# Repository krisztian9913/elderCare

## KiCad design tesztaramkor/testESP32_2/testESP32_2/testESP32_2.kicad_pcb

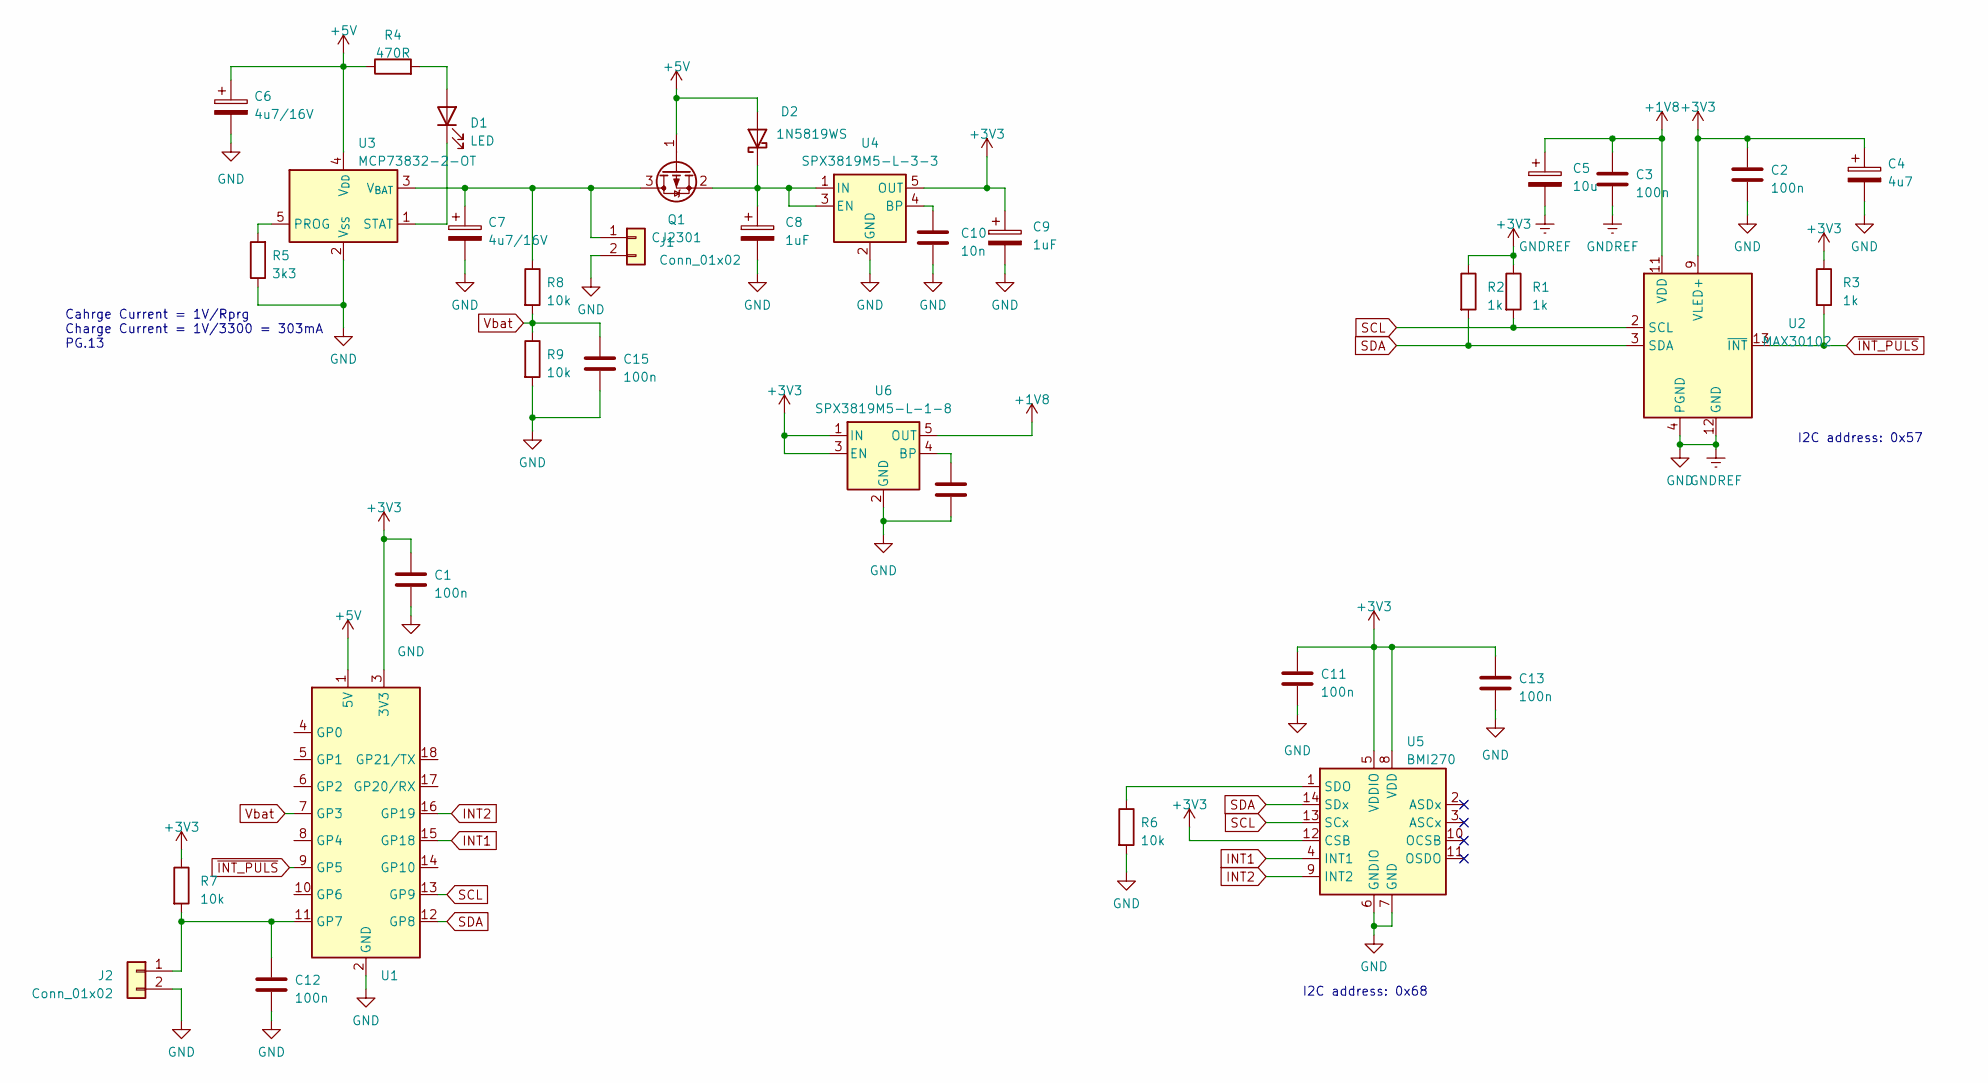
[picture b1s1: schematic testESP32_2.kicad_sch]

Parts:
C1, C2, C3, C11, C12, C13, C15: 100n; C_0603_1608Metric_Pad1.08x0.95mm_HandSolder
C4: 4u7; CP_EIA-3216-18_Kemet-A_Pad1.58x1.35mm_HandSolder
C5: 10u; CP_EIA-3216-18_Kemet-A_Pad1.58x1.35mm_HandSolder
C6, C7: 4u7/16V; CP_EIA-3216-10_Kemet-I_Pad1.58x1.35mm_HandSolder
C8, C9: 1uF; CP_EIA-3216-10_Kemet-I_Pad1.58x1.35mm_HandSolder
C10, C14: 10n; C_0603_1608Metric_Pad1.08x0.95mm_HandSolder
D1: LED; LED_0603_1608Metric_Pad1.05x0.95mm_HandSolder
D2: 1N5819WS; D_SOD-323_HandSoldering
J1, J2: Conn_01x02; PinHeader_1x02_P2.54mm_Vertical
Q1: CJ2301; SOT-23
R1, R2, R3: 1k; R_0603_1608Metric_Pad0.98x0.95mm_HandSolder
R4: 470R; R_0603_1608Metric_Pad0.98x0.95mm_HandSolder
R5: 3k3; R_0603_1608Metric_Pad0.98x0.95mm_HandSolder
R6, R7, R8, R9: 10k; R_0603_1608Metric_Pad0.98x0.95mm_HandSolder
U1: ESP32-C3-Zero
U2: MAX30102; Maxim_OLGA-14_3.3x5.6mm_P0.8mm
U3: MCP73832-2-OT; SOT-23-5
U4: SPX3819M5-L-3-3; SOT-23-5
U5: BMI270; Bosch_LGA-14_3x2.5mm_P0.5mm
U6: SPX3819M5-L-1-8; SOT-23-5

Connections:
+1V8: C3.1, C5.1, U2.11 (VDD), U6.5 (OUT)
+3V3: C1.1, C2.1, C4.1, C9.1, C11.1, C13.1, R1.1, R2.1, R3.1, R7.1, U1.3 (3V3), U2.9 (VLED+), U2.10 (VLED+), U4.5 (OUT), U5.5 (VDDIO), U5.8 (VDD), U5.12 (CSB), U6.1 (IN), U6.3 (EN)
+5V: C6.1, D2.2 (A), Q1.1 (G), R4.1, U1.1 (5V), U3.4 (V_{DD})
GND: C1.2, C2.2, C3.2, C4.2, C5.2, C6.2, C7.2, C8.2, C9.2, C10.2, C11.2, C12.2, C13.2, C14.2, C15.2, J1.2, J2.2, R5.1, R6.2, R9.2, U1.2 (GND), U2.4 (PGND), U2.12 (GND), U3.2 (V_{SS}), U4.2 (GND), U5.6 (GNDIO), U5.7 (GND), U6.2 (GND)
INT1: U1.15 (GP18), U5.4 (INT1)
INT2: U1.16 (GP19), U5.9 (INT2)
unnamed: D1.2 (A), R4.2
unnamed: D1.1 (K), U3.1 (STAT)
unnamed: C8.1, D2.1 (K), Q1.2 (S), U4.1 (IN), U4.3 (EN)
unnamed: C7.1, J1.1, Q1.3 (D), R8.1, U3.3 (V_{BAT})
unnamed: C12.1, J2.1, R7.2, U1.11 (GP7)
unnamed: R5.2, U3.5 (PROG)
unnamed: C10.1, U4.4 (BP)
unnamed: R6.1, U5.1 (SDO)
unnamed: C14.1, U6.4 (BP)
SCL: R1.2, U1.13 (GP9), U2.2 (SCL), U5.13 (SCx)
SDA: R2.2, U1.12 (GP8), U2.3 (SDA), U5.14 (SDx)
Vbat: C15.1, R8.2, R9.1, U1.7 (GP3)
~INT_PULS: R3.2, U1.9 (GP5), U2.13 (~INT)

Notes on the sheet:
Cahrge Current = 1V/Rprg Charge Current = 1V/3300 = 303mA PG.13
I2C address: 0x57
I2C address: 0x68

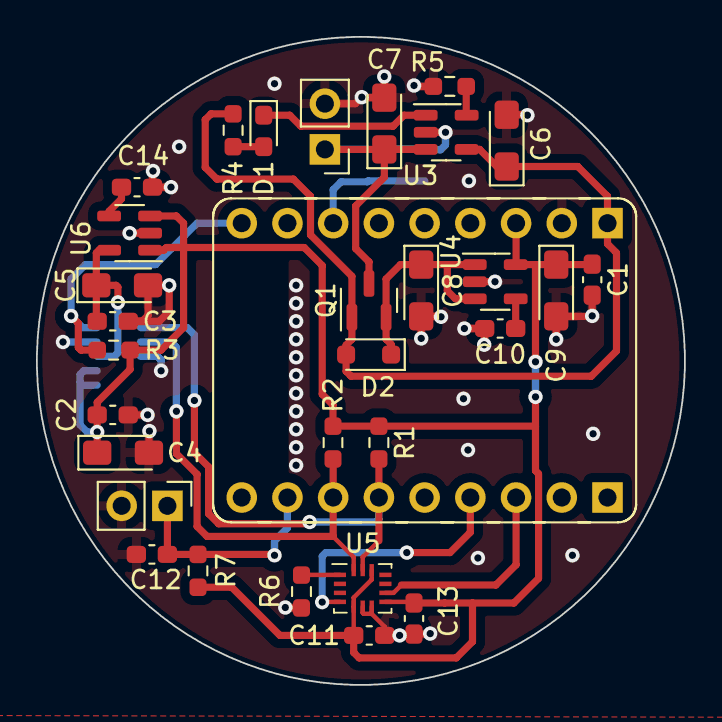
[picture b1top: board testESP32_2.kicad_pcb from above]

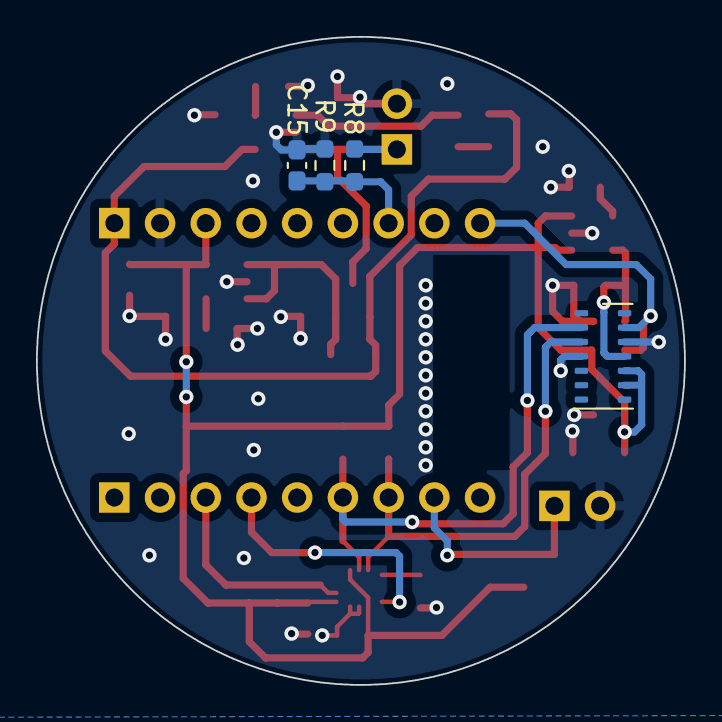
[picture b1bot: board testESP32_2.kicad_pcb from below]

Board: 2 copper layers, 36.0 x 36.0 mm, 35 parts (4 on the bottom side), 19 nets.

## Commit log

2025-05-13 projekt dokumentumok
